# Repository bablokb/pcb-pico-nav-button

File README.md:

Slider and Navigation-Button PCB for the Raspberry Pi Pico
==========================================================

This is a little PCB for the Pico featuring a slider and a 5-way navigational button.

The PCB uses 6 GPIOs: one for the slider, five for the navigational button:

    P1 (SE)        P2  (SW)
    GND            GND
    P3 (NE)        P4  (Down)
    P5 (Slider)    P6  (NW)

There are four options for mounting the PCB on the back of the Pico
(viewing from the back, the high GP-numbers are on the left):

  - GP28-GP26 / GP5-GP7
  - GP22-GP20 / GP12-GP15
  - GP19-GP17 / GP12-GP14 (rotated!)
  - GP18-GP16 / GP13-GP15

KiCAD (V6) files are available in the directory `pico-nav-button`. Ready to use
production files for JLCPCB are in the directory `production_files`.

Schematic and Layout
--------------------

3D-View
-------

License
-------

[![CC BY-SA 4.0][cc-by-sa-shield]][cc-by-sa]

This work is licensed under a
[Creative Commons Attribution-ShareAlike 4.0 International
License][cc-by-sa].

[![CC BY-SA 4.0][cc-by-sa-image]][cc-by-sa]

[cc-by-sa]: http://creativecommons.org/licenses/by-sa/4.0/
[cc-by-sa-image]: https://licensebuttons.net/l/by-sa/4.0/88x31.png
[cc-by-sa-shield]:
https://img.shields.io/badge/License-CC%20BY--SA%204.0-lightgrey.svg

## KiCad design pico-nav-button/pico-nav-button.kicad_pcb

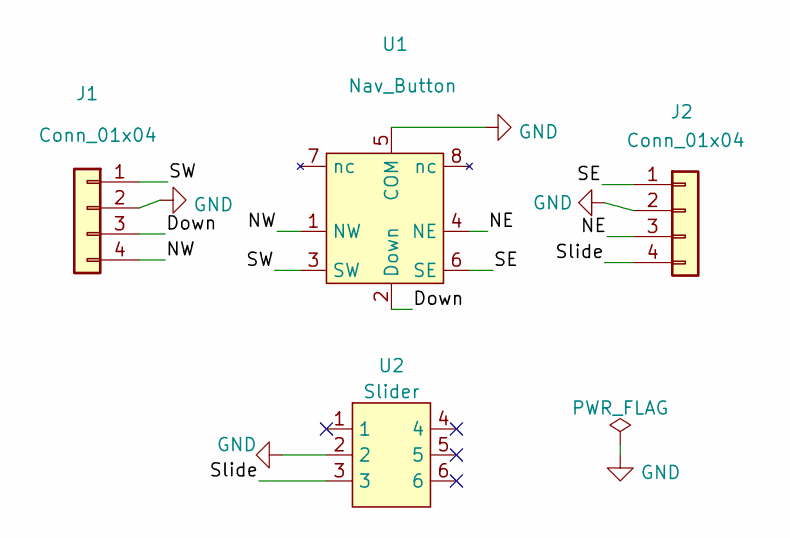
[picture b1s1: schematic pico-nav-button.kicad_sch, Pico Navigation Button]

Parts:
J1, J2: Conn_01x04; PinSocket_1x04_P2.54mm_Vertical
U1: Nav_Button; Nav_Button_5x; LCSC C145898
U2: Slider; LCSC C381098

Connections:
/Down: J1.3, U1.2 (Down)
/NE: J2.3, U1.4 (NE)
/NW: J1.4, U1.1 (NW)
/SE: J2.1, U1.6 (SE)
/SW: J1.1, U1.3 (SW)
/Slide: J2.4, U2.3
GND: J1.2, J2.2, U1.5 (COM), U2.2

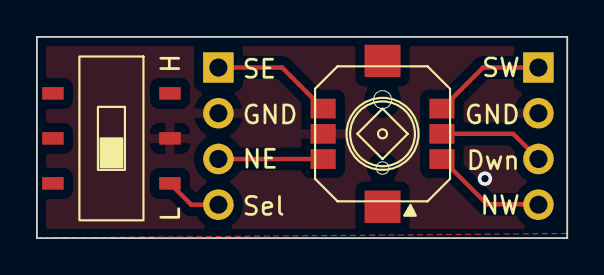
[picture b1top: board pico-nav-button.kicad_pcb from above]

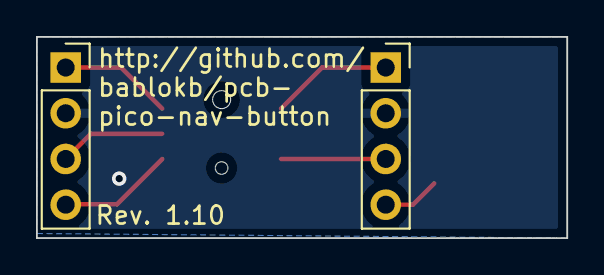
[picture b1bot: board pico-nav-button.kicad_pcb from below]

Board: 2 copper layers, 29.5 x 11.2 mm, 4 parts (2 on the bottom side), 7 nets.

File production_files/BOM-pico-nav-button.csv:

Comment,Designator,Footprint,LCSC
Nav_Button,U1,Nav_Button_5x,C145898
Slider,U2,Slider,C381098
Conn_01x04,J1,PinSocket_1x04_P2.54mm_Vertical,
Conn_01x04,J2,PinSocket_1x04_P2.54mm_Vertical,

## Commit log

2024-04-24 Rev 1.00: initial commit
2024-04-24 Rev 1.10: fixed pad-to-pin assignments
2024-04-24 added example program (CircuitPython)
